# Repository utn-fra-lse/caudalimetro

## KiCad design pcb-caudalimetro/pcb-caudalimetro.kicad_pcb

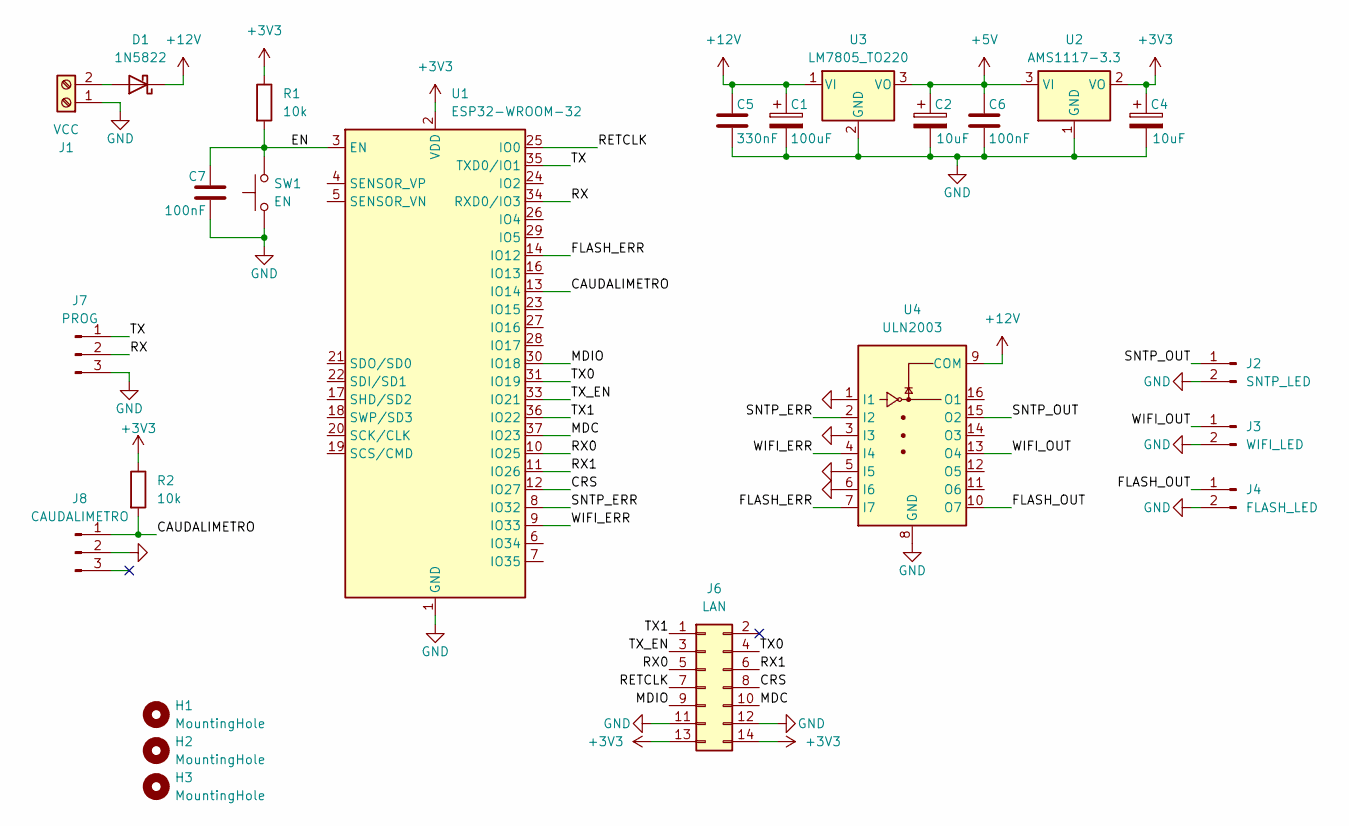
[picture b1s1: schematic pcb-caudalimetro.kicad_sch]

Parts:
C1: 100uF; CP_Radial_D6.3mm_P2.50mm
C2, C4: 10uF; CP_Radial_D6.3mm_P2.50mm
C5: 330nF; C_0805_2012Metric_Pad1.18x1.45mm_HandSolder
C6, C7: 100nF; C_0805_2012Metric_Pad1.18x1.45mm_HandSolder
D1: 1N5822; D_MicroMELF_Handsoldering
H1, H2, H3: MountingHole; MountingHole_3.2mm_M3_DIN965
J1: VCC; TerminalBlock_Phoenix_MKDS-1,5-2-5.08_1x02_P5.08mm_Horizont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
J2: SNTP_LED; Molex_KK-254_AE-6410-02A_1x02_P2.54mm_Vertical
J3: WIFI_LED; Molex_KK-254_AE-6410-02A_1x02_P2.54mm_Vertical
J4: FLASH_LED; Molex_KK-254_AE-6410-02A_1x02_P2.54mm_Vertical
J6: LAN; LAN_Module
J7: PROG; Molex_KK-254_AE-6410-03A_1x03_P2.54mm_Vertical
J8: CAUDALIMETRO; Molex_KK-254_AE-6410-03A_1x03_P2.54mm_Vertical
R1, R2: 10k; R_1206_3216Metric_Pad1.30x1.75mm_HandSolder
SW1: EN; SW_PUSH_6mm
U1: ESP32-WROOM-32; ESP32-WROOM-32E
U2: AMS1117-3.3; SOT-223-3_TabPin2
U3: LM7805_TO220; TO-220-3_Vertical
U4: ULN2003; DIP-16_W7.62mm_Socket

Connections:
+3V3: C4.1, J6.13, J6.14, R1.1, R2.1, U1.2 (VDD), U2.2 (VO)
+5V: C2.1, C6.1, U2.3 (VI), U3.3 (VO)
+12V: C1.1, C5.1, D1.1 (K), U3.1 (VI), U4.9 (COM)
/CAUDALIMETRO: J8.1, R2.2, U1.13 (IO14)
/CRS: J6.8, U1.12 (IO27)
/EN: C7.1, R1.2, SW1.2, U1.3 (EN)
/FLASH_ERR: U1.14 (IO12), U4.7 (I7)
/FLASH_OUT: J4.1, U4.10 (O7)
/MDC: J6.10, U1.37 (IO23)
/MDIO: J6.9, U1.30 (IO18)
/RETCLK: J6.7, U1.25 (IO0)
/RX: J7.2, U1.34 (RXD0/IO3)
/RX0: J6.5, U1.10 (IO25)
/RX1: J6.6, U1.11 (IO26)
/SNTP_ERR: U1.8 (IO32), U4.2 (I2)
/SNTP_OUT: J2.1, U4.15 (O2)
/TX: J7.1, U1.35 (TXD0/IO1)
/TX0: J6.4, U1.31 (IO19)
/TX1: J6.1, U1.36 (IO22)
/TX_EN: J6.3, U1.33 (IO21)
/WIFI_ERR: U1.9 (IO33), U4.4 (I4)
/WIFI_OUT: J3.1, U4.13 (O4)
GND: C1.2, C2.2, C4.2, C5.2, C6.2, C7.2, J1.1, J2.2, J3.2, J4.2, J6.11, J6.12, J7.3, J8.2, SW1.1, U1.1 (GND), U1.15 (GND), U1.38 (GND), U1.39 (GND), U2.1 (GND), U3.2 (GND), U4.1 (I1), U4.3 (I3), U4.5 (I5), U4.6 (I6), U4.8 (GND)
unnamed: D1.2 (A), J1.2

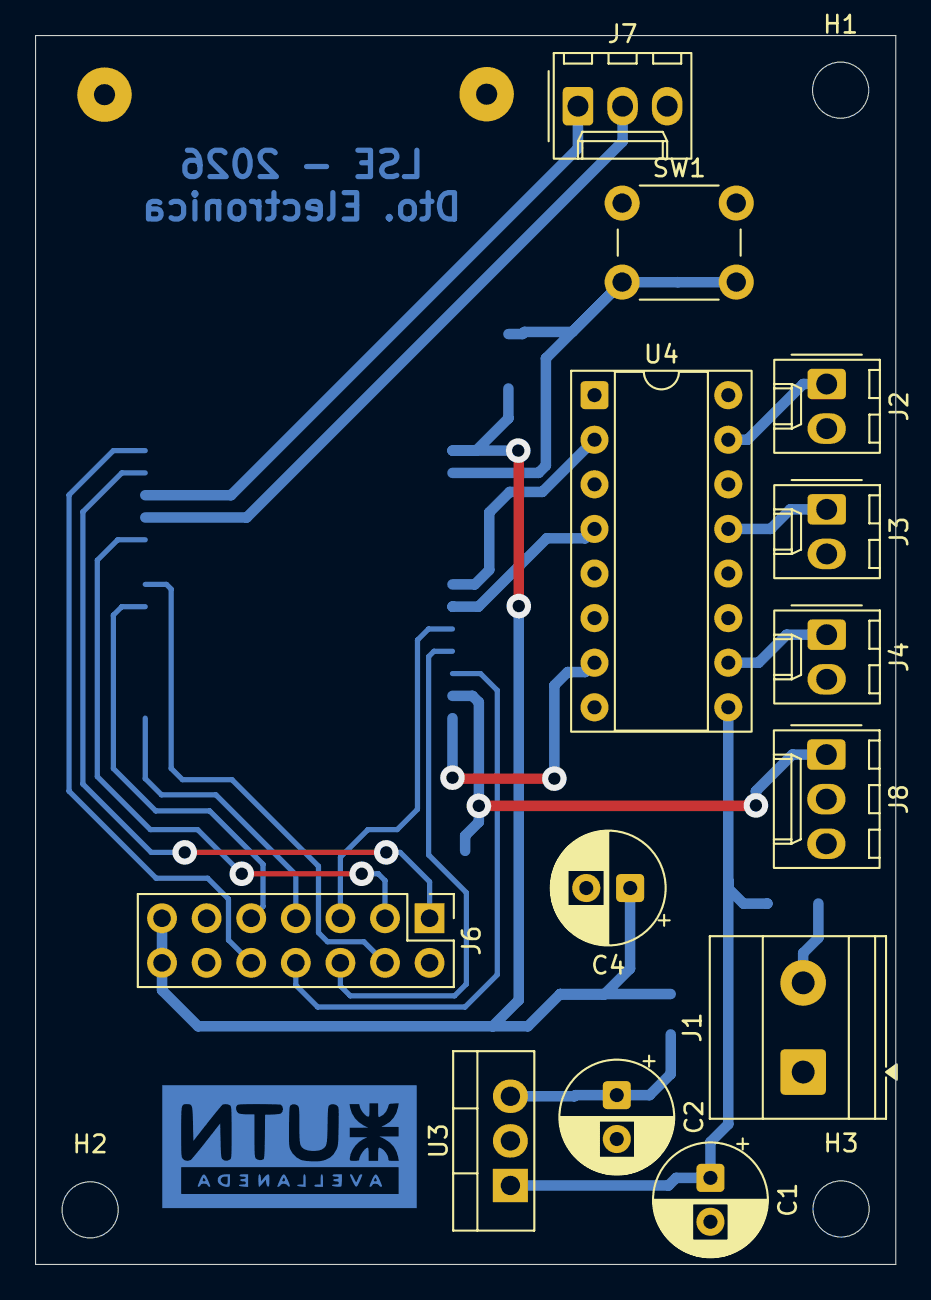
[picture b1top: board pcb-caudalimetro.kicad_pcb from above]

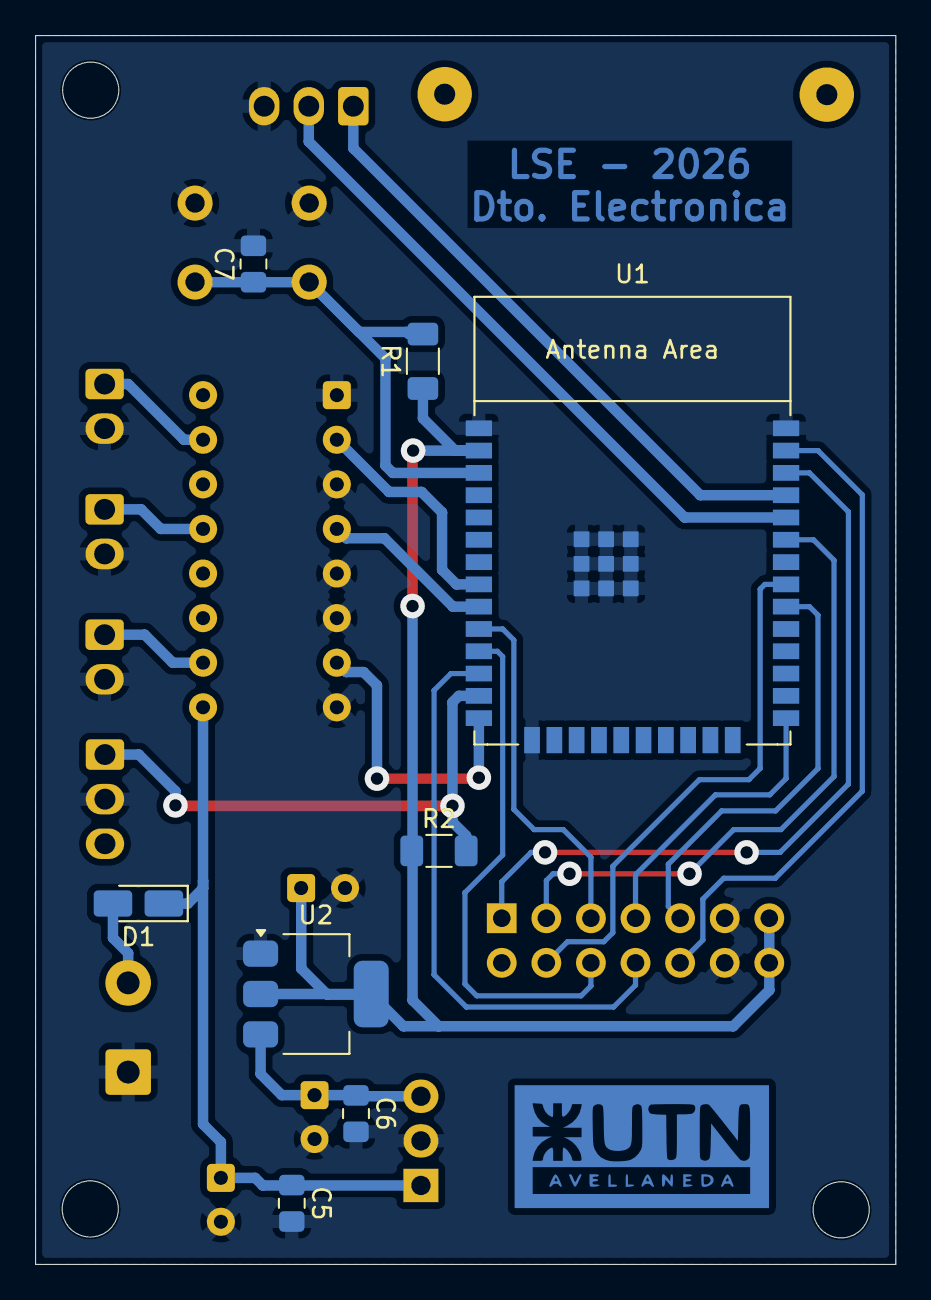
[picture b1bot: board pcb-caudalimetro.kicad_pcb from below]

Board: 2 copper layers, 49.0 x 70.0 mm, 24 parts (8 on the bottom side), 24 nets.
